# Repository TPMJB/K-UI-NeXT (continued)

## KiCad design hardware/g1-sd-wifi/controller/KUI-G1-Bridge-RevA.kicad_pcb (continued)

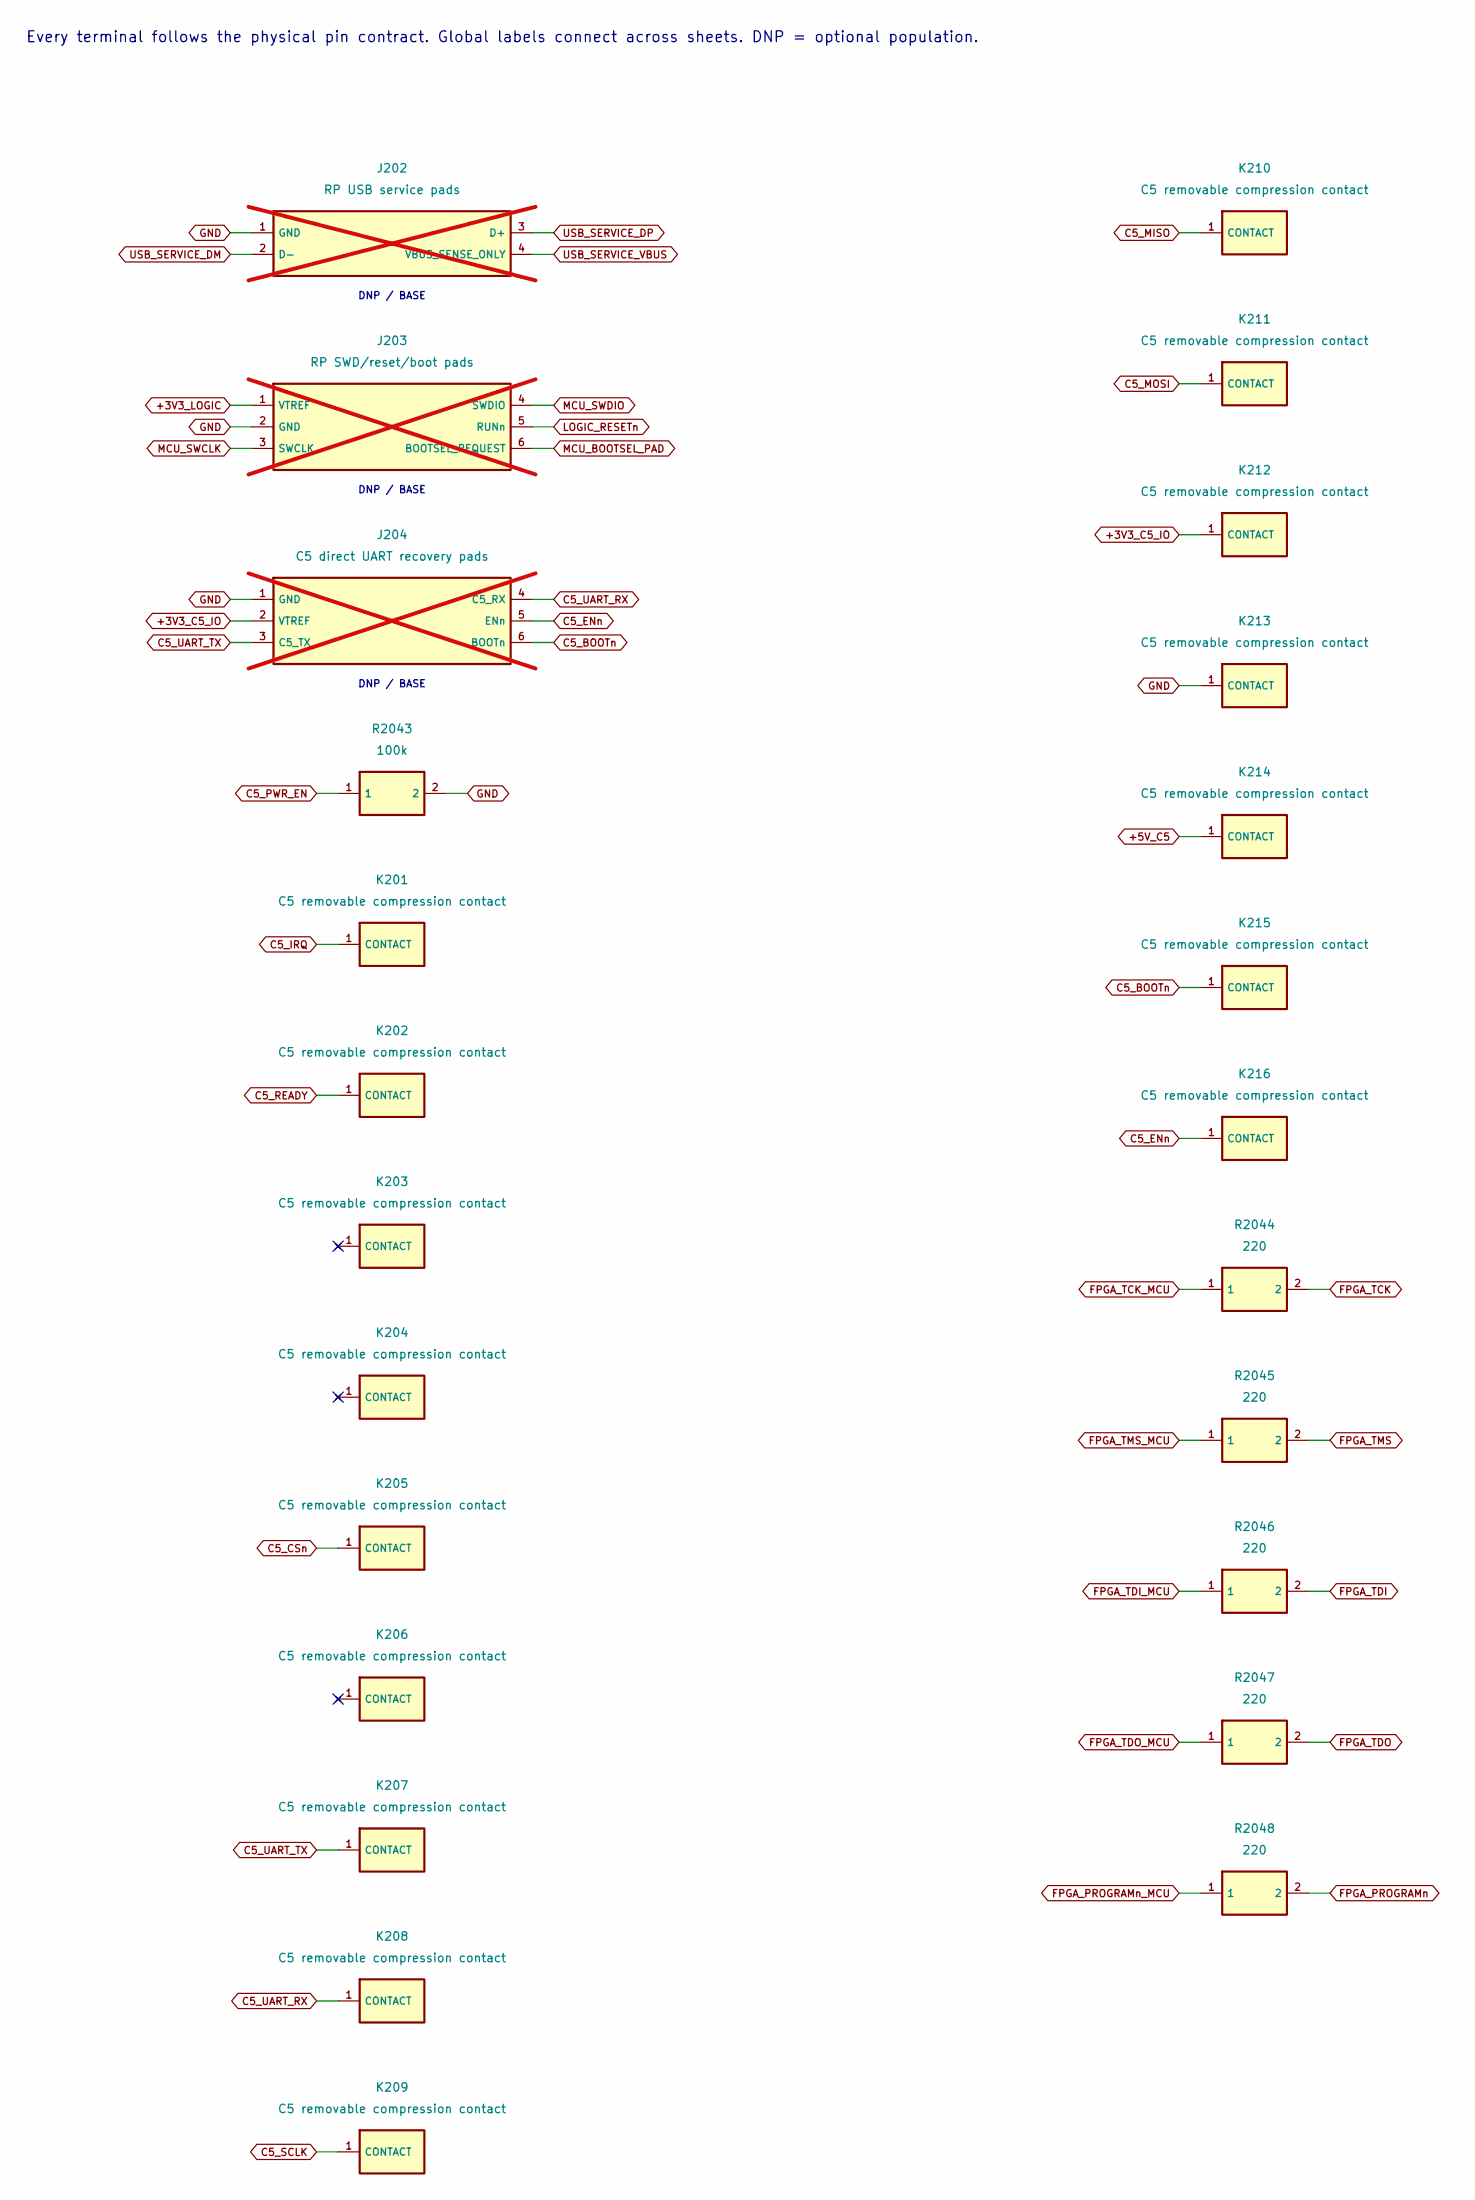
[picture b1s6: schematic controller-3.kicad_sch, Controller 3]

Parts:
J202: RP USB service pads; Service_USB_4Pad; MPN CUSTOM_USB_SERVICE_PADS; not fitted
J203: RP SWD/reset/boot pads; Service_SWD_6Pad; MPN CUSTOM_SWD_SERVICE_PADS; not fitted
J204: C5 direct UART recovery pads; Service_C5_6Pad; MPN CUSTOM_C5_SERVICE_PADS; not fitted
K201, K202, K203, K204, K205, K206, K207, K208, K209, K210, K211, K212, K213, K214, K215, K216: C5 removable compression contact; Harwin_S7221-45R_BodyOrigin; MPN S7221-45R
R2043: 100k; R_0402_1005Metric; MPN RC0402FR-07100KL
R2044, R2045, R2046, R2047, R2048: 220; R_0402_1005Metric; MPN RC0402FR-07220RL

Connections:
+3V3_C5_IO: J204.2 (VTREF), K212.1; also elsewhere on the board
+3V3_LOGIC: J203.1 (VTREF); also elsewhere on the board
+5V_C5: K214.1; also elsewhere on the board
C5_BOOTn: J204.6 (BOOTn), K215.1; also elsewhere on the board
C5_CSn: K205.1; also elsewhere on the board
C5_ENn: J204.5 (ENn), K216.1; also elsewhere on the board
C5_IRQ: K201.1; also elsewhere on the board
C5_MISO: K210.1; also elsewhere on the board
C5_MOSI: K211.1; also elsewhere on the board
C5_PWR_EN: R2043.1; also elsewhere on the board
C5_READY: K202.1; also elsewhere on the board
C5_SCLK: K209.1; also elsewhere on the board
C5_UART_RX: J204.4 (C5_RX), K208.1; also elsewhere on the board
C5_UART_TX: J204.3 (C5_TX), K207.1; also elsewhere on the board
FPGA_PROGRAMn: R2048.2; also elsewhere on the board
FPGA_PROGRAMn_MCU: R2048.1; also elsewhere on the board
FPGA_TCK: R2044.2; also elsewhere on the board
FPGA_TCK_MCU: R2044.1; also elsewhere on the board
FPGA_TDI: R2046.2; also elsewhere on the board
FPGA_TDI_MCU: R2046.1; also elsewhere on the board
FPGA_TDO: R2047.2; also elsewhere on the board
FPGA_TDO_MCU: R2047.1; also elsewhere on the board
FPGA_TMS: R2045.2; also elsewhere on the board
FPGA_TMS_MCU: R2045.1; also elsewhere on the board
GND: J202.1 (GND), J203.2 (GND), J204.1 (GND), K213.1, R2043.2; also elsewhere on the board
LOGIC_RESETn: J203.5 (RUNn); also elsewhere on the board
MCU_BOOTSEL_PAD: J203.6 (BOOTSEL_REQUEST); also elsewhere on the board
MCU_SWCLK: J203.3 (SWCLK); also elsewhere on the board
MCU_SWDIO: J203.4 (SWDIO); also elsewhere on the board
USB_SERVICE_DM: J202.2 (D-); also elsewhere on the board
USB_SERVICE_DP: J202.3 (D+); also elsewhere on the board
USB_SERVICE_VBUS: J202.4 (VBUS_SENSE_ONLY); also elsewhere on the board

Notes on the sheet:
Every terminal follows the physical pin contract. Global labels connect across sheets. DNP = optional population.
DNP / BASE

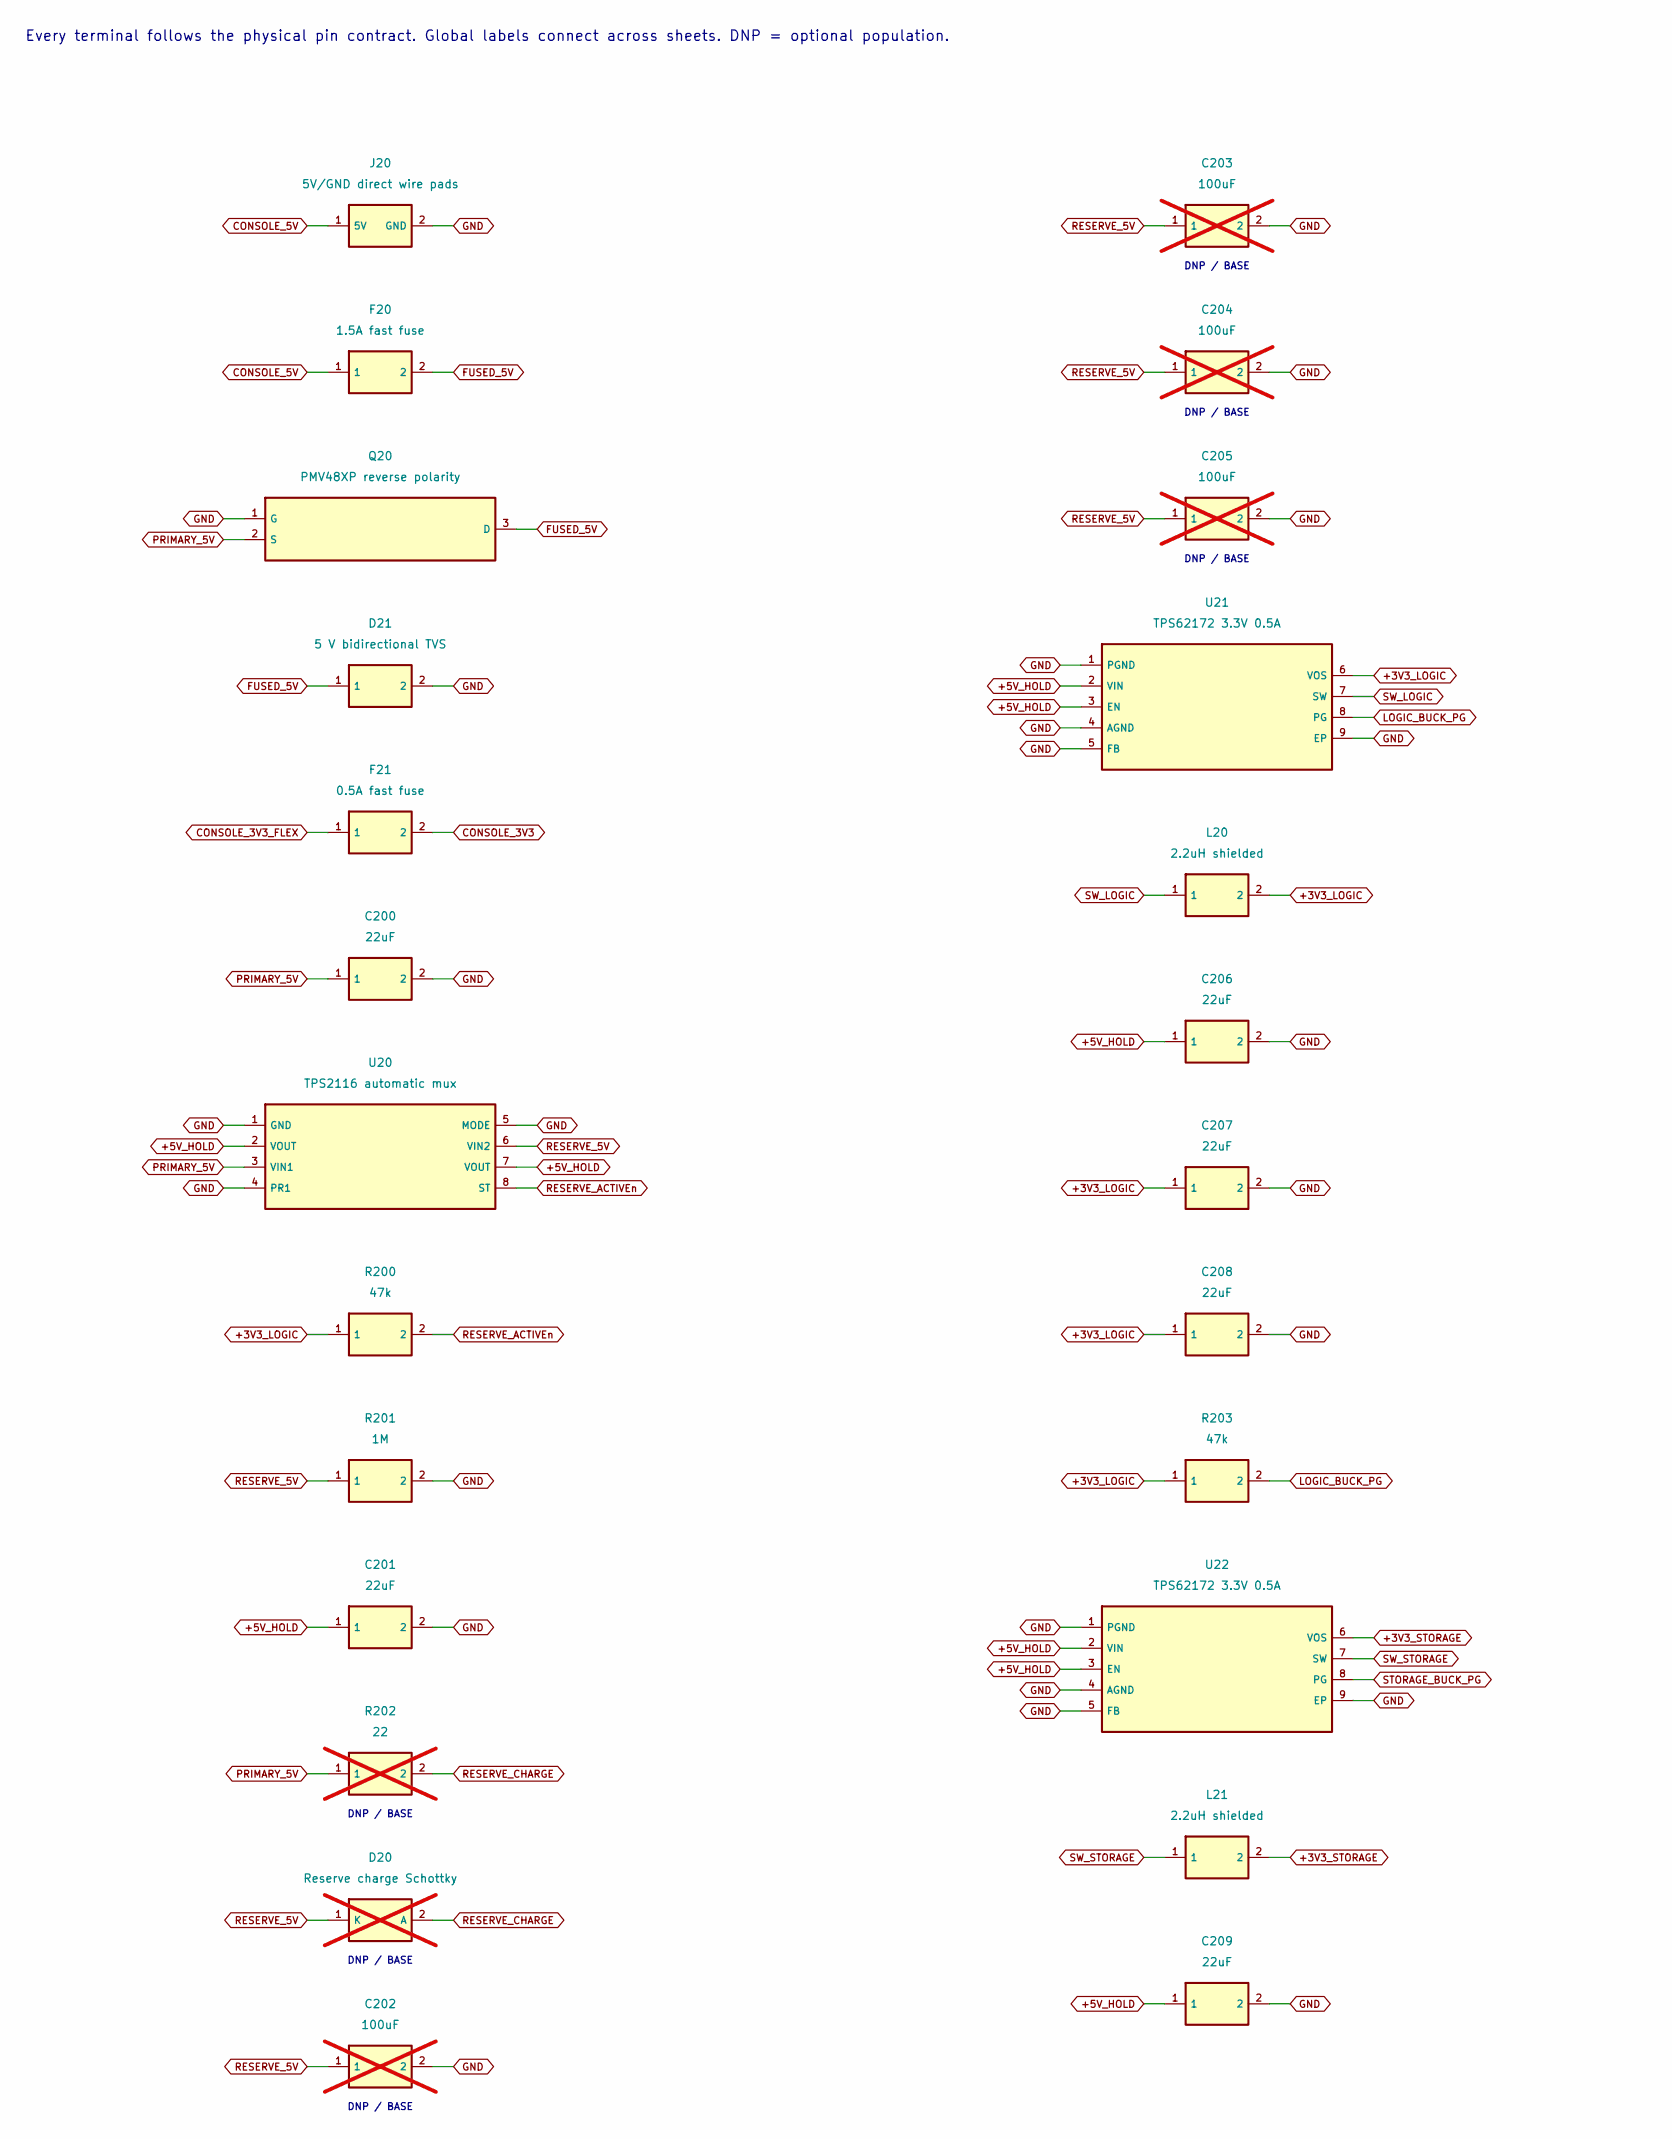
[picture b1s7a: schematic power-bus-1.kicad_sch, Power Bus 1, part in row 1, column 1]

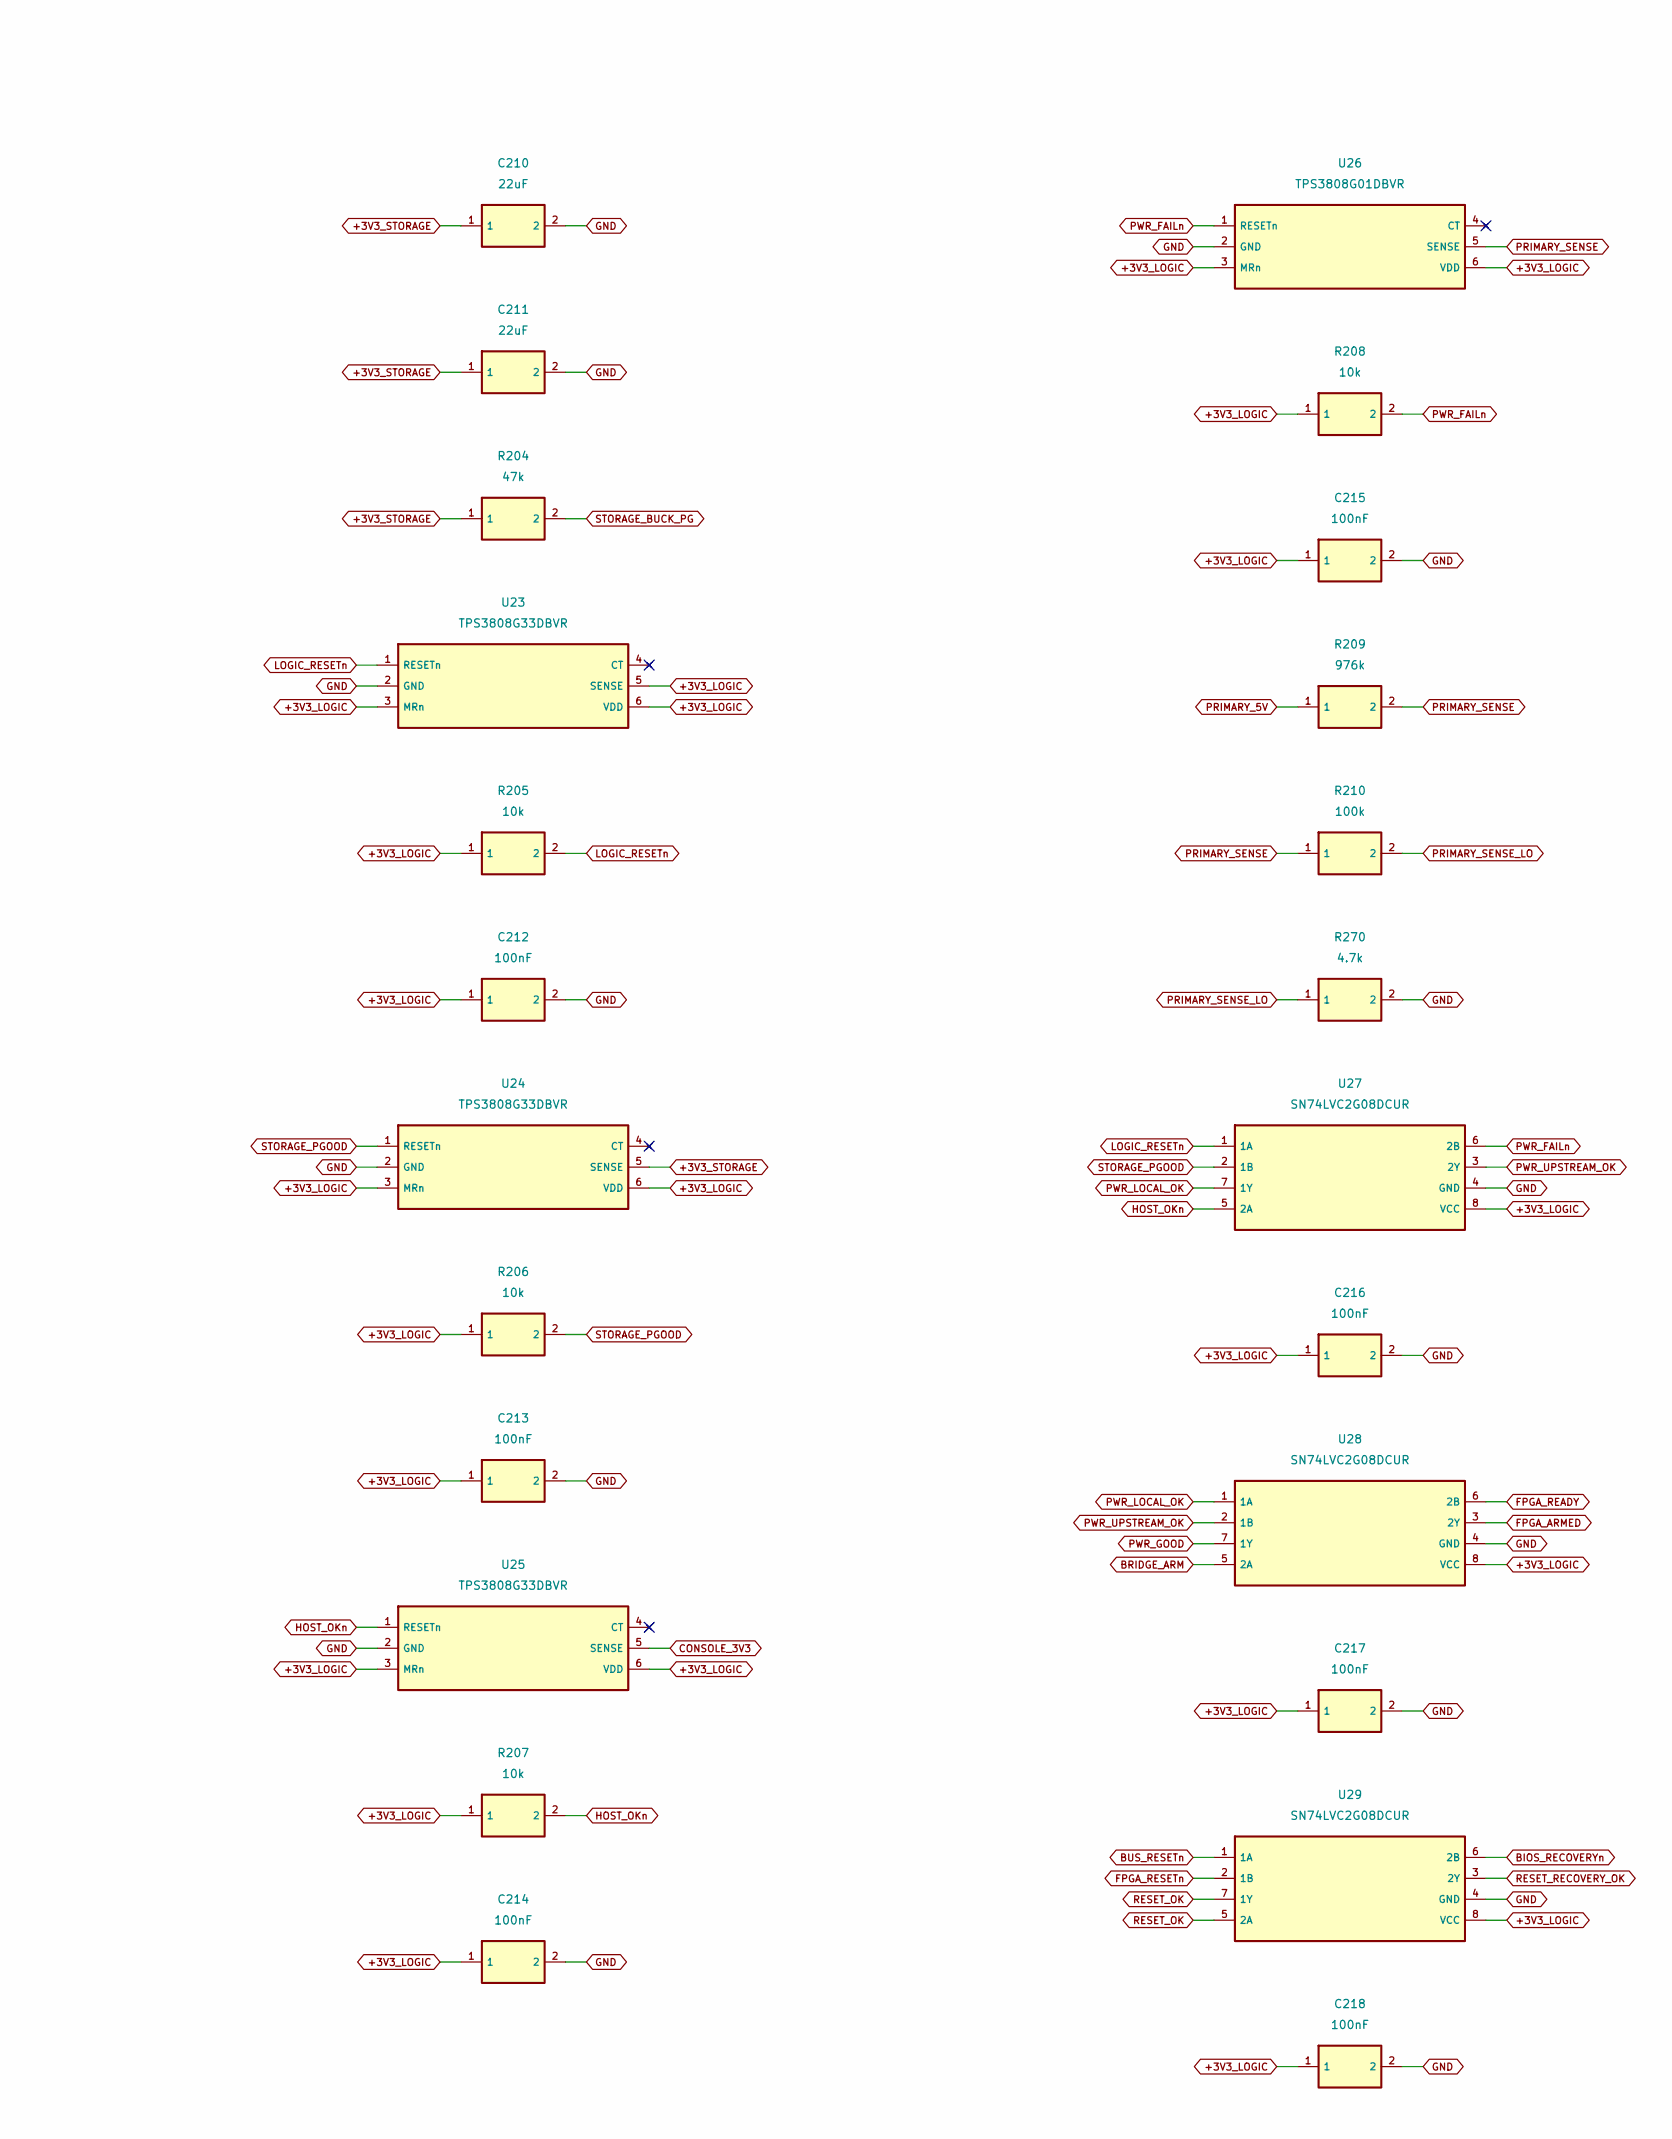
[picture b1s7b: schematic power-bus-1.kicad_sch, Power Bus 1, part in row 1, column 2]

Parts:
C200, C201, C206, C207, C208, C209, C210, C211: 22uF; C_0805_2012Metric; MPN GRM21BR61A226ME51L
C202, C203, C204, C205: 100uF; C_1210_3225Metric; MPN GRM32ER61A107ME20L; not fitted
C212, C213, C214, C215, C216, C217, C218: 100nF; C_0402_1005Metric; MPN GRM155R71C104KA88D
D20: Reserve charge Schottky; Nexperia_CFP3_SOD-123W; MPN PMEG2010ER,115; not fitted
D21: 5 V bidirectional TVS; HighDiode_SMF_SOD123FL; MPN SMF5.0CA; LCSC C22458622
F20: 1.5A fast fuse; Littelfuse_467_0603_Recommended; MPN 046701.5NR
F21: 0.5A fast fuse; Littelfuse_467_0603_Recommended; MPN 0467.500NR; LCSC C206990
J20: 5V/GND direct wire pads; Power_Wire_Pads_2x2mm; MPN PCB solder pads; no fitted connector
L20, L21: 2.2uH shielded; Coilcraft_XFL3012; MPN XFL3012-222MEC
Q20: PMV48XP reverse polarity; SOT-23; MPN PMV48XP,215
R200, R203, R204: 47k; R_0402_1005Metric; MPN RC0402FR-0747KL
R201: 1M; R_0402_1005Metric; MPN RC0402FR-071ML
R202: 22; R_0805_2012Metric; MPN RC0805FR-0722RL; not fitted
R205, R206, R207, R208: 10k; R_0402_1005Metric; MPN RC0402FR-0710KL
R209: 976k; R_0402_1005Metric; MPN RC0402FR-07976KL
R210: 100k; R_0402_1005Metric; MPN RC0402FR-07100KL
R270: 4.7k; R_0402_1005Metric; MPN RC0402FR-074K7L
U20: TPS2116 automatic mux; TI_DRL0008A; MPN TPS2116DRLR
U21, U22: TPS62172 3.3V 0.5A; TI_DSG0008A; MPN TPS62172DSGR
U23, U24, U25: TPS3808G33DBVR; SOT-23-6; MPN TPS3808G33DBVR
U26: TPS3808G01DBVR; SOT-23-6; MPN TPS3808G01DBVR
U27, U28, U29: SN74LVC2G08DCUR; VSSOP-8_2.3x2mm_P0.5mm; MPN SN74LVC2G08DCUR

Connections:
+3V3_LOGIC: C207.1, C208.1, C212.1, C213.1, C214.1, C215.1, C216.1, C217.1, C218.1, L20.2, R200.1, R203.1, R205.1, R206.1, R207.1, R208.1, U21.6 (VOS), U23.3 (MRn), U23.5 (SENSE), U23.6 (VDD), U24.3 (MRn), U24.6 (VDD), U25.3 (MRn), U25.6 (VDD), U26.3 (MRn), U26.6 (VDD), U27.8 (VCC), U28.8 (VCC), U29.8 (VCC); also elsewhere on the board
+3V3_STORAGE: C210.1, C211.1, L21.2, R204.1, U22.6 (VOS), U24.5 (SENSE); also elsewhere on the board
+5V_HOLD: C201.1, C206.1, C209.1, U20.2 (VOUT), U20.7 (VOUT), U21.2 (VIN), U21.3 (EN), U22.2 (VIN), U22.3 (EN); also elsewhere on the board
BIOS_RECOVERYn: U29.6 (2B); also elsewhere on the board
BRIDGE_ARM: U28.5 (2A); also elsewhere on the board
BUS_RESETn: U29.1 (1A); also elsewhere on the board
CONSOLE_3V3: F21.2, U25.5 (SENSE); also elsewhere on the board
CONSOLE_3V3_FLEX: F21.1; also elsewhere on the board
CONSOLE_5V: F20.1, J20.1 (5V)
FPGA_ARMED: U28.3 (2Y); also elsewhere on the board
FPGA_READY: U28.6 (2B); also elsewhere on the board
FPGA_RESETn: U29.2 (1B); also elsewhere on the board
FUSED_5V: D21.1, F20.2, Q20.3 (D)
GND: C200.2, C201.2, C202.2, C203.2, C204.2, C205.2, C206.2, C207.2, C208.2, C209.2, C210.2, C211.2, C212.2, C213.2, C214.2, C215.2, C216.2, C217.2, C218.2, D21.2, J20.2 (GND), Q20.1 (G), R201.2, R270.2, U20.1 (GND), U20.4 (PR1), U20.5 (MODE), U21.1 (PGND), U21.4 (AGND), U21.5 (FB), U21.9 (EP), U22.1 (PGND), U22.4 (AGND), U22.5 (FB), U22.9 (EP), U23.2 (GND), U24.2 (GND), U25.2 (GND), U26.2 (GND), U27.4 (GND), U28.4 (GND), U29.4 (GND); also elsewhere on the board
HOST_OKn: R207.2, U25.1 (RESETn), U27.5 (2A)
LOGIC_BUCK_PG: R203.2, U21.8 (PG)
LOGIC_RESETn: R205.2, U23.1 (RESETn), U27.1 (1A); also elsewhere on the board
PRIMARY_5V: C200.1, Q20.2 (S), R202.1, R209.1, U20.3 (VIN1); also elsewhere on the board
PRIMARY_SENSE: R209.2, R210.1, U26.5 (SENSE)
PRIMARY_SENSE_LO: R210.2, R270.1
PWR_FAILn: R208.2, U26.1 (RESETn), U27.6 (2B); also elsewhere on the board
PWR_GOOD: U28.7 (1Y); also elsewhere on the board
PWR_LOCAL_OK: U27.7 (1Y), U28.1 (1A)
PWR_UPSTREAM_OK: U27.3 (2Y), U28.2 (1B)
RESERVE_5V: C202.1, C203.1, C204.1, C205.1, D20.1 (K), R201.1, U20.6 (VIN2); also elsewhere on the board
RESERVE_ACTIVEn: R200.2, U20.8 (ST)
RESERVE_CHARGE: D20.2 (A), R202.2
RESET_OK: U29.5 (2A), U29.7 (1Y)
RESET_RECOVERY_OK: U29.3 (2Y); also elsewhere on the board
STORAGE_BUCK_PG: R204.2, U22.8 (PG)
STORAGE_PGOOD: R206.2, U24.1 (RESETn), U27.2 (1B); also elsewhere on the board
SW_LOGIC: L20.1, U21.7 (SW)
SW_STORAGE: L21.1, U22.7 (SW)

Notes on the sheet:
Every terminal follows the physical pin contract. Global labels connect across sheets. DNP = optional population.
DNP / BASE
